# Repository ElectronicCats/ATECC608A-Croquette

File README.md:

# Electronic Cats Croquette ATECC608

PCB files for the Electronic Cats Croquette ATECC608. 

Format is KiCAD schematic and board layout

## Description

The ATECC608 is the latest crypto-auth chip from Microchip, and it uses I2C to send/receive commands. Once you 'lock' the chip with your details, you can use it for ECDH and AES-128 encrypt/decrypt/signing. There's also hardware support for random number generation, and SHA-256/HMAC hash functions to  greatly speed up a slower micro's cryptography commands.

### Features:
- Cryptographic co-processor with secure hardware-based key storage
- Protected storage for up to 16 Keys, certificates or data
- ECDH: FIPS SP800-56A Elliptic Curve Diffie-Hellman
- NIST standard P256 elliptic curve support
- SHA-256 & HMAC hash including off-chip context save/restore
- AES-128: encrypt/decrypt, galois field multiply for GCM

## How to contribute 
 Contributions are welcome! 

Please read the document  [**Contribution Manual**](https://github.com/ElectronicCats/electroniccats-cla/blob/main/electroniccats-contribution-manual.md)  which will show you how to contribute your changes to the project.

✨ Thanks to all our [contributors](https://github.com/ElectronicCats/ATECC608A-Croquette/graphs/contributors)! ✨

See  [**_Electronic Cats CLA_**](https://github.com/ElectronicCats/electroniccats-cla/blob/main/electroniccats-cla.md) for more information.

See the [**community code of conduct**](https://github.com/ElectronicCats/electroniccats-cla/blob/main/electroniccats-community-code-of-conduct.md)   for a vision of the community we want to build and what we expect from it.

### Maintainer

Electronic Cats invests time and resources in providing this open-source design design, please support Electronic Cats and open-source hardware by purchasing products from Electronic Cats!

## License

Hardware released under an CERN Open Hardware Licence v1.2. See the LICENSE_HARDWARE file for more information.

Electronic Cats is a registered trademark, please do not use if you sell these PCBs.

3 Sept 2019

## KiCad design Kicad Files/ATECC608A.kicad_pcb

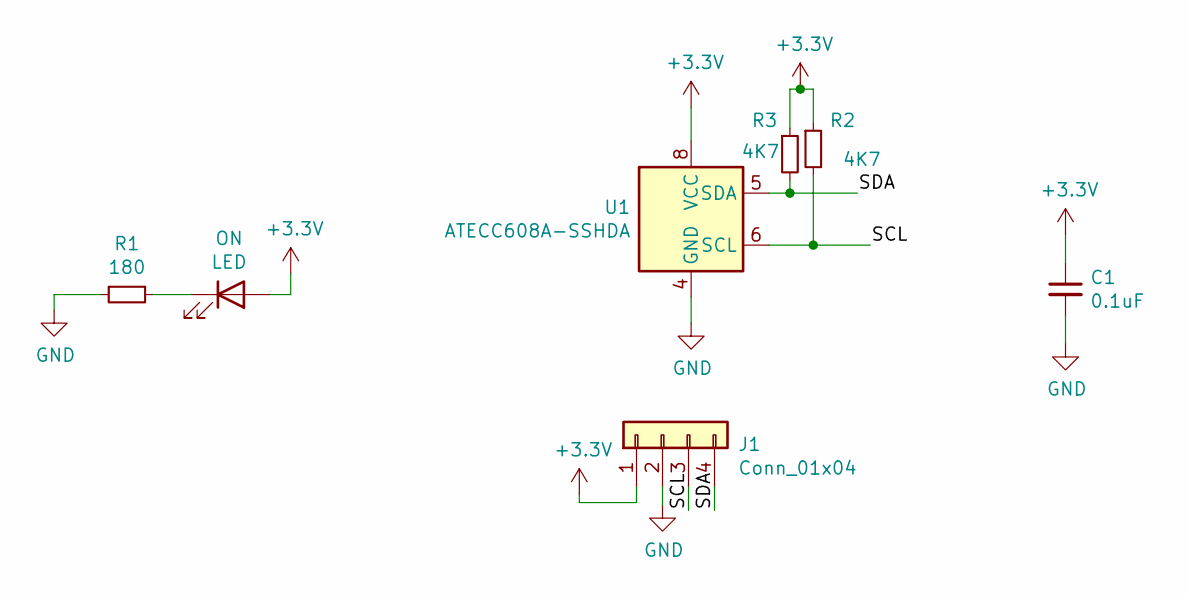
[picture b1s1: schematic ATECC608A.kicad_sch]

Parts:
C1: 0.1uF; C_0805_2012Metric_Pad1.15x1.40mm_HandSolder
J1: Conn_01x04; PinHeader_1x04_P2.54mm_Vertical
ON: LED; LED_0805_2012Metric_Pad1.15x1.40mm_HandSolder
R1: 180; R_0805_2012Metric_Pad1.15x1.40mm_HandSolder
R2, R3: 4K7; R_0805_2012Metric_Pad1.15x1.40mm_HandSolder
U1: ATECC608A-SSHDA; SOIC-8_3.9x4.9mm_P1.27mm

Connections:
+3V3: C1.1, J1.1, ON.2 (A), R2.1, R3.1, U1.8 (VCC)
/SCL: J1.3, R2.2, U1.6 (SCL)
/SDA: J1.4, R3.2, U1.5 (SDA)
GND: C1.2, J1.2, R1.2, U1.4 (GND)
unnamed: ON.1 (K), R1.1

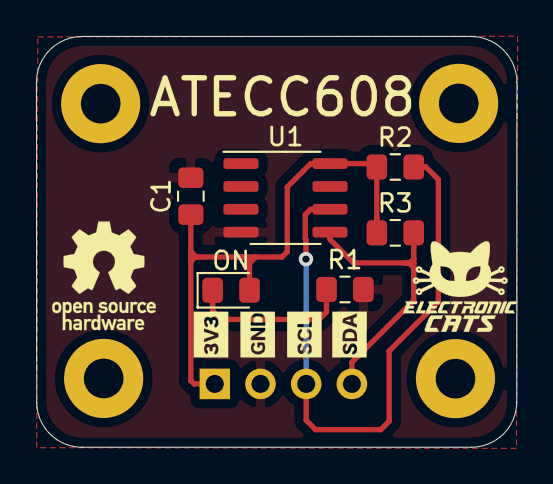
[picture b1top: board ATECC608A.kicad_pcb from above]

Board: 2 copper layers, 26.7 x 22.8 mm, 7 parts (1 on the bottom side), 5 nets.

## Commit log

2019-09-03 Schematic ready
2019-09-19 Change name LED1 and netlist
2019-09-19 Desing rules and contour pcb
2019-09-20 add logo EC
2019-10-23 Change of measures
2019-10-24 accommodation screws
2019-10-24 initial routeo
2019-10-24 add logos
2019-10-24 add pins logos
2019-10-25 logos review
2019-10-25 logos
2019-11-05 add logo front
2020-09-03 Update README.md
    Added license
